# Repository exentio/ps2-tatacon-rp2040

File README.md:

# PS2 Tatacon RP2040 converter
---

Replacement PCB for the PS2 Tatacon (NPC-107) using the Waveshare RP2040-Zero.  
The recommended firmware is GP2040-CE, which provides sub-ms input lag and
allows to use it with both PC and many consoles. The used pins are as follows:  

| Controller Input    | RP2040 Pin |
|---------------------|------------|
| Right Don           | 7          |
| Left Don            | 8          |
| Right Ka            | 27         |
| Left Ka             | 26         |
| Start (yellow wire) | 14         |
| Select (red wire)   | 15         |

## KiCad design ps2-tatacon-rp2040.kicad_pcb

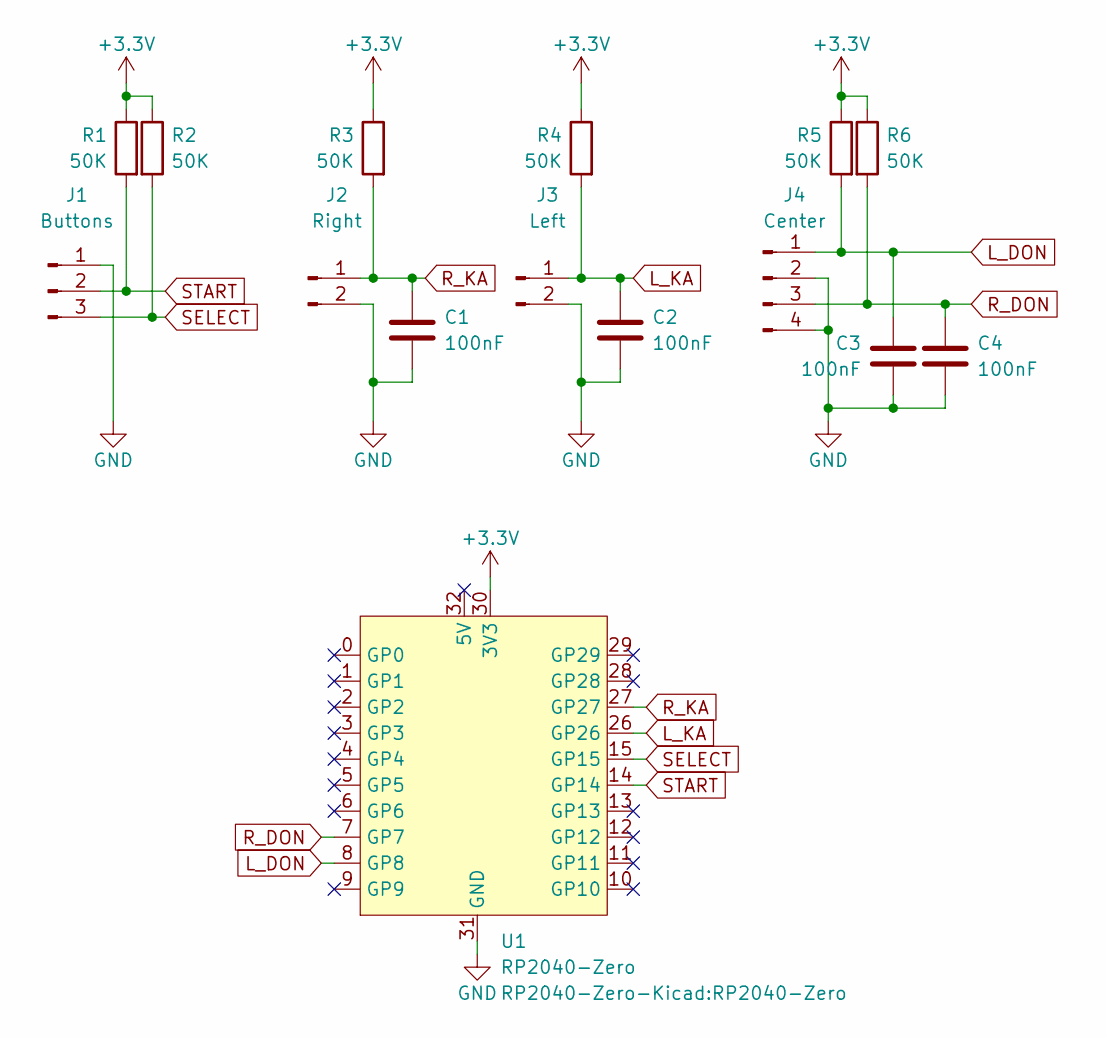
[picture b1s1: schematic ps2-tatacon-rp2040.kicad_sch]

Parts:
C1, C2, C3, C4: 100nF; C_0603_1608Metric_Pad1.08x0.95mm_HandSolder
J1: Buttons; PinSocket_1x03_P2.54mm_Vertical
J2: Right; PinSocket_1x02_Spaced_P2.00mm
J3: Left; PinSocket_1x02_Spaced_P2.00mm
J4: Center; PinSocket_1x04_P2.5mm_Vertical
R1, R2, R3, R4, R5, R6: 50K; R_0603_1608Metric_Pad0.98x0.95mm_HandSolder
U1: RP2040-Zero

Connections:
+3.3V: R1.1, R2.1, R3.1, R4.1, R5.1, R6.1, U1.30 (3V3)
GND: C1.2, C2.2, C3.2, C4.2, J1.1, J2.2, J3.2, J4.2, J4.4, U1.31 (GND)
L_DON: C3.1, J4.1, R5.2, U1.8 (GP8)
L_KA: C2.1, J3.1, R4.2, U1.26 (GP26)
R_DON: C4.1, J4.3, R6.2, U1.7 (GP7)
R_KA: C1.1, J2.1, R3.2, U1.27 (GP27)
SELECT: J1.3, R2.2, U1.15 (GP15)
START: J1.2, R1.2, U1.14 (GP14)

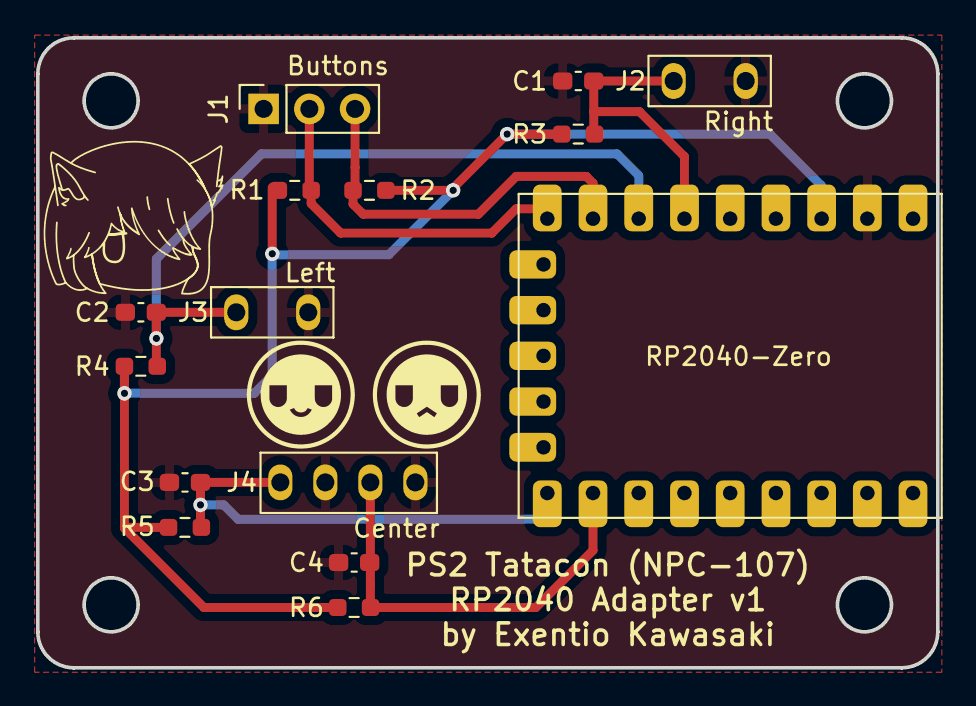
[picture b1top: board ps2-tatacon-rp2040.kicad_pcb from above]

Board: 2 copper layers, 50.0 x 35.0 mm, 15 parts (0 on the bottom side), 8 nets.

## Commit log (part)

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2024-12-11 Inital board layout
2024-12-11 Board layout finished, need to fix footprint
2024-12-12 First revision finished
2024-12-14 Added readme
2024-12-14 Added license
2024-12-15 Better image
2024-12-17 Readme update (start/select wire colors)
2025-01-02 Readme typo
